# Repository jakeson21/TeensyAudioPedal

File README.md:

# TeensyAudioPedal
Project space for custom Teensy based audio pedal

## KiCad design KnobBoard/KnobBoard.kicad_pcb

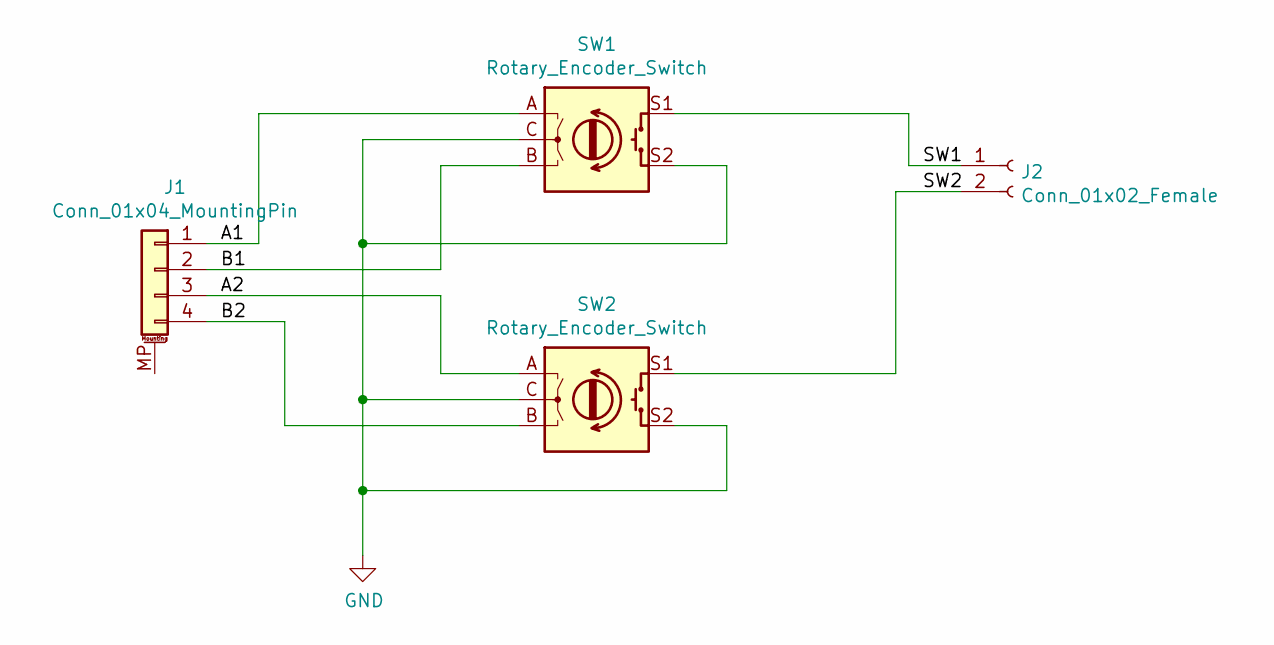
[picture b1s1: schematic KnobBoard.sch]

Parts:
J1: Conn_01x04_MountingPin; Pin_Header_Straight_1x04_Pitch2.54mm
J2: Conn_01x02_Female; Pin_Header_Straight_1x02_Pitch2.54mm
SW1, SW2: Rotary_Encoder_Switch; KSA_Tactile_SPST_12mm

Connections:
/A1: J1.1, SW1.A
/A2: J1.3, SW2.A
/B1: J1.2, SW1.B
/B2: J1.4, SW2.B
/SW1: J2.1, SW1.S1
/SW2: J2.2, SW2.S1
GND: SW1.C, SW1.S2, SW2.C, SW2.S2

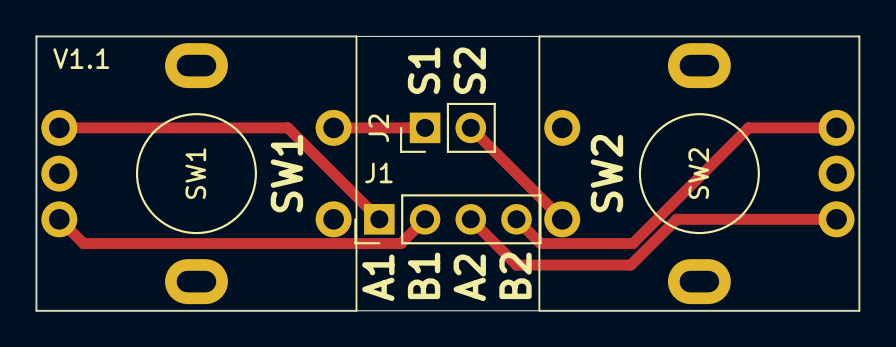
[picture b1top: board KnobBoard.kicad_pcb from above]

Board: 2 copper layers, 45.7 x 15.2 mm, 4 parts (0 on the bottom side), 7 nets.

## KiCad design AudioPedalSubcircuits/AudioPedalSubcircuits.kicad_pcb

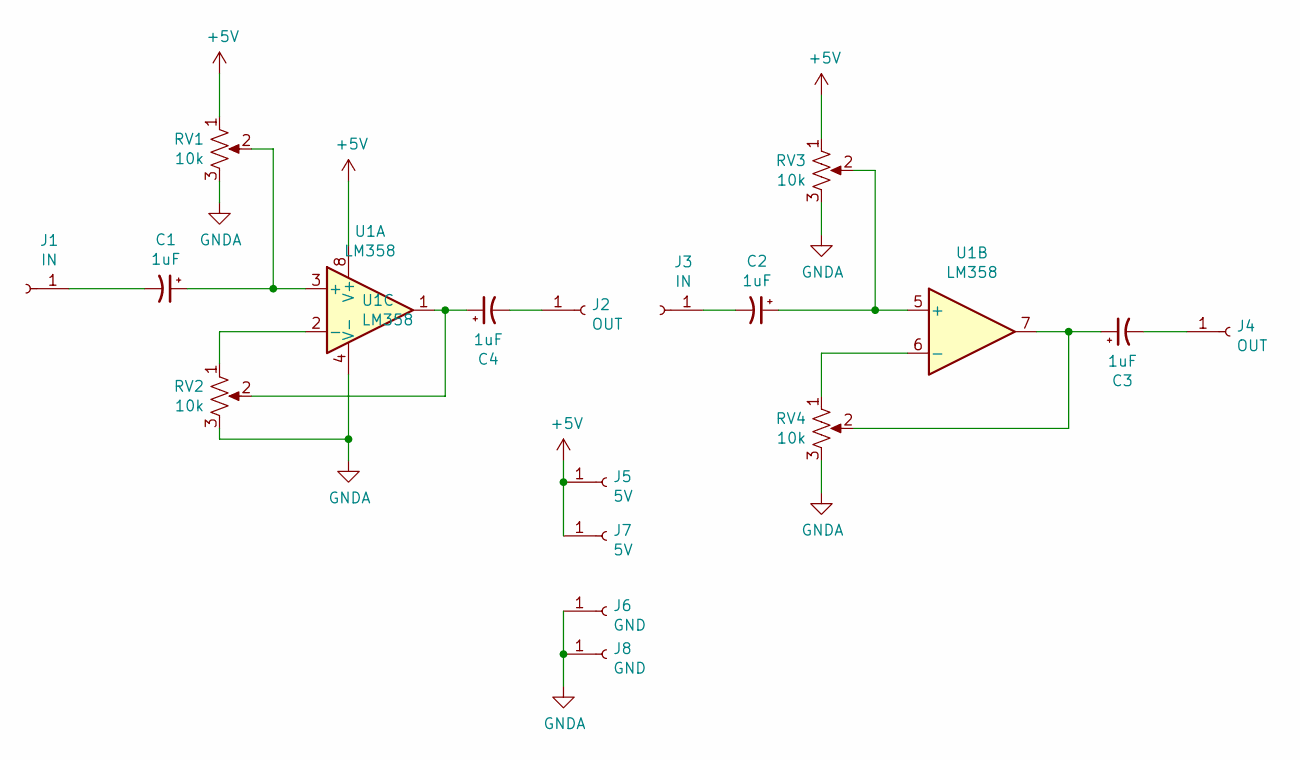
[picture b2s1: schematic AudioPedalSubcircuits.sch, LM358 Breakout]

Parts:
C1, C2, C3, C4: 1uF; CP_Radial_D5.0mm_P2.50mm
J1, J3: IN; Pin_Header_Straight_1x01_Pitch2.54mm
J2, J4: OUT; Pin_Header_Straight_1x01_Pitch2.54mm
J5, J7: 5V; Pin_Header_Straight_1x01_Pitch2.54mm
J6, J8: GND; Pin_Header_Straight_1x01_Pitch2.54mm
RV1, RV2, RV3, RV4: 10k; Potentiometer_Triwood_RM-065
U1: LM358; DIP-8_W7.62mm_Socket

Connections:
+5V: J5.1, J7.1, RV1.1, RV3.1, U1.8 (V+)
GNDA: J6.1, J8.1, RV1.3, RV2.3, RV3.3, RV4.3, U1.4 (V-)
unnamed: C1.1, RV1.2, U1.3 (+)
unnamed: C1.2, J1.1
unnamed: C2.1, RV3.2, U1.5 (+)
unnamed: C2.2, J3.1
unnamed: C3.1, RV4.2, U1.7
unnamed: C3.2, J4.1
unnamed: C4.1, RV2.2, U1.1
unnamed: C4.2, J2.1
unnamed: RV2.1, U1.2 (-)
unnamed: RV4.1, U1.6 (-)

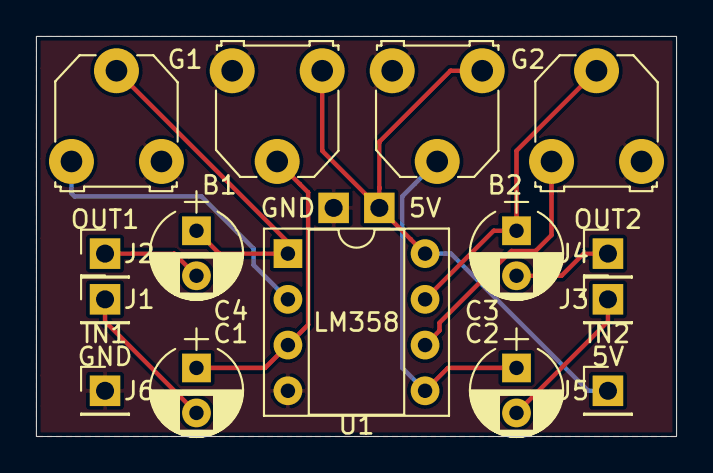
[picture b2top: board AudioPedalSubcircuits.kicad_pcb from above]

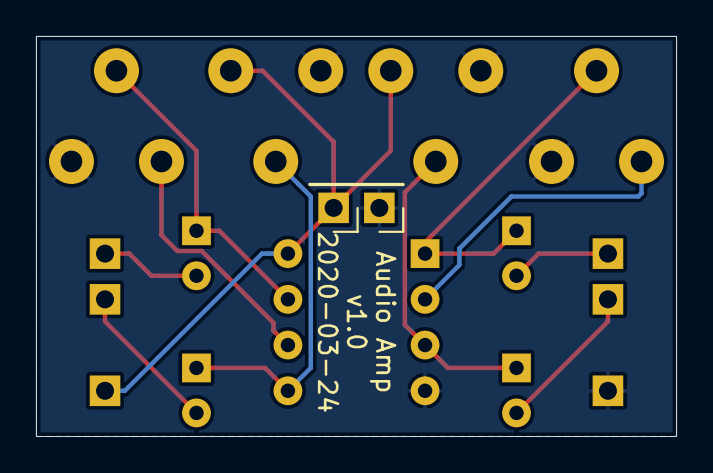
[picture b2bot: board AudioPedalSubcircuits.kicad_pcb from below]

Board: 2 copper layers, 35.6 x 22.2 mm, 17 parts (2 on the bottom side), 12 nets.

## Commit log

2021-10-11 Created rotary encoder board
2021-10-13 tweaks to footprint
2021-11-12 Adding Docs and updates to footprints
2021-11-12 Wires to AMP board
